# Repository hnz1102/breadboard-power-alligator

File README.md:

<div align="center">
  <h1><code>BREAD BOARD POWER ALLIGATOR</code></h1>
  
</div>

# BREAD BOARD POWER ALLIGATOR : Power Supply for Bread-Board

This is power supplies for bread-board. They are designed to be used with a USB PD power supply. The output voltage is from 3.3V to 20V, and the output current is maximum 1A. The output voltage is fixed each adoptor. I made 6 adapters for bread-board power supply. The adapters are 3.3V, 5V, 9V, 12V, 15V, and 20V. The adapters are connected to the bread-board such an alligator clips. It is easy to set up the power supply for the bread-board. If you use a USB PD power supply, you can use over 9V output. If it is not USB PD, you can use only 3.3V or 5V.

The PCB is designed by KiCad. The PCB is common to all adapters. 

## How to use
Just connect a USB PD power supply to the USB-C connector. Then, connect the adoptor to the bread-board. The output voltage is fixed each adoptor. If it turns on the power supply, the LED lights up. 

Be careful to connect the adoptor to the bread-board. The inside of the bread-board power line is +, so connect it so that the top is -. Also, be careful not to connect different adapters to the same bread-board.

## Schematic
[Schematic PDF File](doc/schematic.pdf)

Each adoptor has a different output voltage. The output voltage is determined by any of the following parts.

|Output Voltage|U102|D102|C101|C104|R103|R104|R105|R106|JP101|JP102|
|---|---|--|--|--|--|--|--|--|--|--|
|3.3V|AZ1117CH-3.3|CUS10F3D|DNP|10uF|1K|DNP|0|DNP|OPEN|SHUNT|
|5V|DNP|DNP|DNP|DNP|1K|DNP|DNP|DNP|SHUNT|SHUNT|
|9V|DNP|DNP|1uF|DNP|2K|1K|DNP|20K|SHUNT|OPEN|
|12V|DNP|DNP|1uF|DNP|2K|1K|DNP|47K|SHUNT|OPEN|
|15V|DNP|DNP|1uF|DNP|2K|1K|DNP|100K|SHUNT|OPEN|
|20V|DNP|DNP|1uF|DNP|2K|1K|DNP|200K|SHUNT|OPEN|

*1 DNP: Do Not Populate
*2 R107 is DNP for all adapters.

If you want to change the output voltage, you can change the parts of the table.
e.g If you want to change the output voltage to 1.8V or 2.5V, you can change the parts as follows.
|Output Voltage|U102|D102|C101|C104|R103|R104|R105|R106|JP101|JP102|
|---|---|--|--|--|--|--|--|--|--|--|
|1.8V|AZ1117CH-1.8|CUS10F3D|DNP|10uF|1K|DNP|0|DNP|OPEN|SHUNT|
|2.5V|AZ1117CH-2.5|CUS10F3D|DNP|10uF|1K|DNP|0|DNP|OPEN|SHUNT|

## PCB

*3 In the photo, the PCB is designed to accommodate a Switch, but it was removed from the PCB layout because a compatible Switch could not be found.

# Container

There are STL data for 3D printer in the `stl` directory.
bottom.stl is the bottom of the container. upper-al-xx.stl is the upper of the container like alligator clips. upper-simple_xx.stl is the upper of the container like a battery form.

## LICENSE
Hardware Schematic Documents are licensed under CC-BY-SA V4.0.

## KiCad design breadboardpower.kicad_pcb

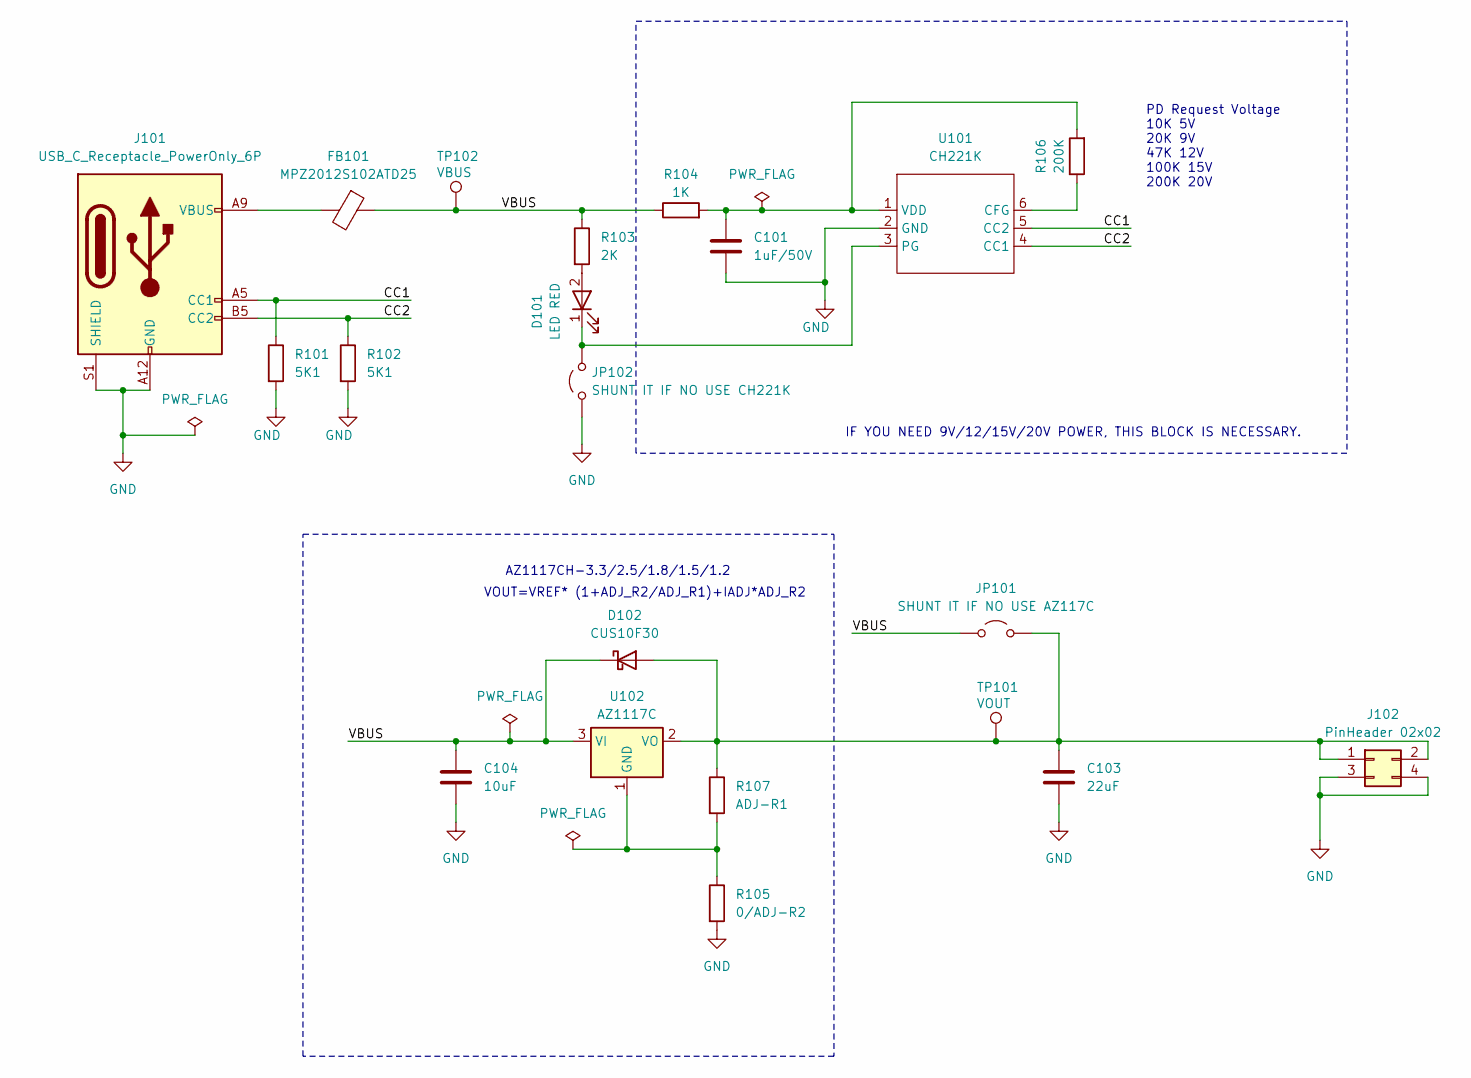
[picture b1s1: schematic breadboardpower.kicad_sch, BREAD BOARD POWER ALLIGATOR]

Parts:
C101: 1uF/50V; C_0805_2012Metric; digikey 311-1886-1-ND
C103: 22uF; C_0805_2012Metric; digikey 311-1903-1-ND
C104: 10uF; C_0805_2012Metric; digikey 311-1869-1-ND
D101: LED RED; LED_0603_1608Metric_Pad1.05x0.95mm_HandSolder; digikey 3147-B1931URO-20D000114U1930CT-ND
D102: CUS10F30; D_SOD-323; digikey CUS10F30H3FCT-ND
FB101: MPZ2012S102ATD25; R_0805_2012Metric; digikey 445-MPZ2012S102ATD25CT-ND
J101: USB_C_Receptacle_PowerOnly_6P; CUI_UJC-HP-3-SMT-TR; digikey 2223-UJC-HP-3-SMT-CT-ND
J102: PinHeader 02x02; PinHeader_2x02_P2.54mm_Vertical; digikey 2057-PH2-04-UA-ND
JP101: SHUNT IT IF NO USE AZ117C; SolderJumper-2_P1.3mm_Open_RoundedPad1.0x1.5mm
JP102: SHUNT IT IF NO USE CH221K; SolderJumper-2_P1.3mm_Open_RoundedPad1.0x1.5mm
R101, R102: 5K1; R_0603_1608Metric; digikey 311-5.10KHRCT-ND
R103: 2K; R_0603_1608Metric; digikey 311-2.0KGRCT-ND
R104: 1K; R_0603_1608Metric; digikey 311-1.00KHRCT-ND
R105: 0/ADJ-R2; R_0603_1608Metric; digikey 311-0.0GRCT-ND
R106: 200K; R_0603_1608Metric; digikey 311-200KHRCT-ND
R107: ADJ-R1; R_0603_1608Metric
TP101: VOUT; TestPoint_Pad_D1.0mm
TP102: VBUS; TestPoint_Pad_D1.0mm
U101: CH221K; SOT-23-6
U102: AZ1117C; SOT-223-3_TabPin2; digikey 497-17239-1-ND

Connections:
/CC1: J101.A5 (CC1), R101.1, U101.5 (CC2)
/CC2: J101.B5 (CC2), R102.1, U101.4 (CC1)
/VBUS: C104.1, D102.1 (K), FB101.1, JP101.1 (A), R103.1, R104.1, TP102.1, U102.3 (VI)
GND: C101.2, C103.2, C104.2, J101.A12 (GND), J101.B12 (GND), J101.S1 (SHIELD), J102.3, J102.4, JP102.1 (A), R101.2, R102.2, R105.2, U101.2 (GND)
unnamed: D101.2 (A), R103.2
unnamed: D101.1 (K), JP102.2 (B), U101.3 (PG)
unnamed: C103.1, D102.2 (A), J102.1, J102.2, JP101.2 (B), R107.1, TP101.1, U102.2 (VO)
unnamed: FB101.2, J101.A9 (VBUS), J101.B9 (VBUS)
unnamed: R106.1, U101.6 (CFG)
unnamed: C101.1, R104.2, R106.2, U101.1 (VDD)
unnamed: R105.1, R107.2, U102.1 (GND)

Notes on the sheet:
VOUT=VREF* (1+ADJ_R2/ADJ_R1)+IADJ*ADJ_R2
IF YOU NEED 9V/12/15V/20V POWER, THIS BLOCK IS NECESSARY.
PD Request Voltage 10K 5V 20K 9V 47K 12V 100K 15V 200K 20V
AZ1117CH-3.3/2.5/1.8/1.5/1.2

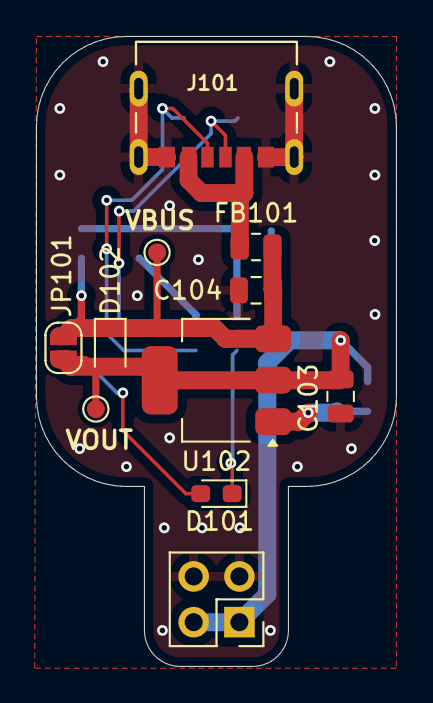
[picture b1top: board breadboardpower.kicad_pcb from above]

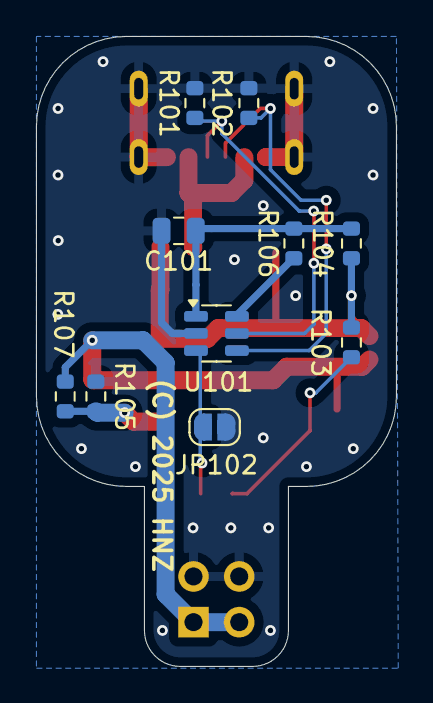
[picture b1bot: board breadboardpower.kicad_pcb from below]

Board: 2 copper layers, 20.0 x 35.0 mm, 21 parts (10 on the bottom side), 11 nets.

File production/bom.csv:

"Reference","Value","Footprint","Qty","digikey","distributor"
"C101","1uF/50V","Capacitor_SMD:C_0805_2012Metric","1","311-1886-1-ND","https://www.digikey.com/en/products/detail/yageo/CC0805KKX7R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"
"C103","22uF","Capacitor_SMD:C_0805_2012Metric","1","311-1903-1-ND","https://www.digikey.com/en/products/detail/yageo/CC0805MKX5R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"
"C104","10uF","Capacitor_SMD:C_0805_2012Metric","1","311-1869-1-ND","https://www.digikey.com/en/products/detail/yageo/CC0805KKX5R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"
"D101","LED RED","LED_SMD:LED_0603_1608Metric_Pad1.05x0.95mm_HandSolder","1","3147-B1931URO-20D000114U1930CT-ND","https://www.digikey.com/en/products/detail/harvatek-corporat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"
"D102","CUS10F30","Diode_SMD:D_SOD-323","1","CUS10F30H3FCT-ND","https://www.digikey.com/en/products/detail/toshiba-semicondu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"
"FB101","MPZ2012S102ATD25","Resistor_SMD:R_0805_2012Metric","1","445-MPZ2012S102ATD25CT-ND","https://www.digikey.com/en/products/detail/tdk-corporation/M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"
"J101","USB_C_Receptacle_PowerOnly_6P","Library:CUI_UJC-HP-3-SMT-TR","1","2223-UJC-HP-3-SMT-CT-ND","https://www.digikey.com/en/products/detail/same-sky-formerly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"
"J102","PinHeader 02x02","Connector_PinHeader_2.54mm:PinHeader_2x02_P2.54mm_Vertical","1","2057-PH2-04-UA-ND","https://www.digikey.com/en/products/detail/adam-tech/PH2-04-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"
"JP101","SHUNT IT IF NO USE AZ117C","Jumper:SolderJumper-2_P1.3mm_Open_RoundedPad1.0x1.5mm","1","-","-"
"JP102","SHUNT IT IF NO USE CH221K","Jumper:SolderJumper-2_P1.3mm_Open_RoundedPad1.0x1.5mm","1","-","-"
"R101,R102","5K1","Resistor_SMD:R_0603_1608Metric","2","311-5.10KHRCT-ND","https://www.digikey.com/en/products/detail/yageo/RC0603FR-07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"
"R103","2K","Resistor_SMD:R_0603_1608Metric","1","311-2.0KGRCT-ND","https://www.digikey.com/en/products/detail/yageo/RC0603JR-07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"
"R104","1K","Resistor_SMD:R_0603_1608Metric","1","311-1.00KHRCT-ND","https://www.digikey.com/en/products/detail/yageo/RC0603FR-07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"
"R105","0/ADJ-R2","Resistor_SMD:R_0603_1608Metric","1","311-0.0GRCT-ND","https://www.digikey.com/en/products/detail/yageo/RC0603JR-07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"
"R106","200K","Resistor_SMD:R_0603_1608Metric","1","311-200KHRCT-ND","https://www.digikey.com/en/products/detail/yageo/RC0603FR-07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"
"R107","ADJ-R1","Resistor_SMD:R_0603_1608Metric","1","-","-"
"TP101","VOUT","TestPoint:TestPoint_Pad_D1.0mm","1","-","-"
"TP102","VBUS","TestPoint:TestPoint_Pad_D1.0mm","1","-","-"
"U101","CH221K","Package_TO_SOT_SMD:SOT-23-6","1","-","https://jlcpcb.com/partdetail/WCH_Nanjing_Qinheng-CH221K/C5125736"
"U102","AZ1117C","Package_TO_SOT_SMD:SOT-223-3_TabPin2","1","497-17239-1-ND","https://www.digikey.com/en/products/detail/stmicroelectronic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"

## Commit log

2025-02-12 Add front image
2025-02-12 Add schematic PDF file
2025-02-14 Fixed typo

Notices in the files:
breadboardpower.kicad_pcb:
(C) 2025 HNZ
breadboardpower.kicad_sch:
(C) 2025 Hiroshi Nakajima
